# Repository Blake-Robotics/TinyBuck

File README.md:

# TinyBuck
A three channel Buck based high power led driver, with included AtTiny for programming

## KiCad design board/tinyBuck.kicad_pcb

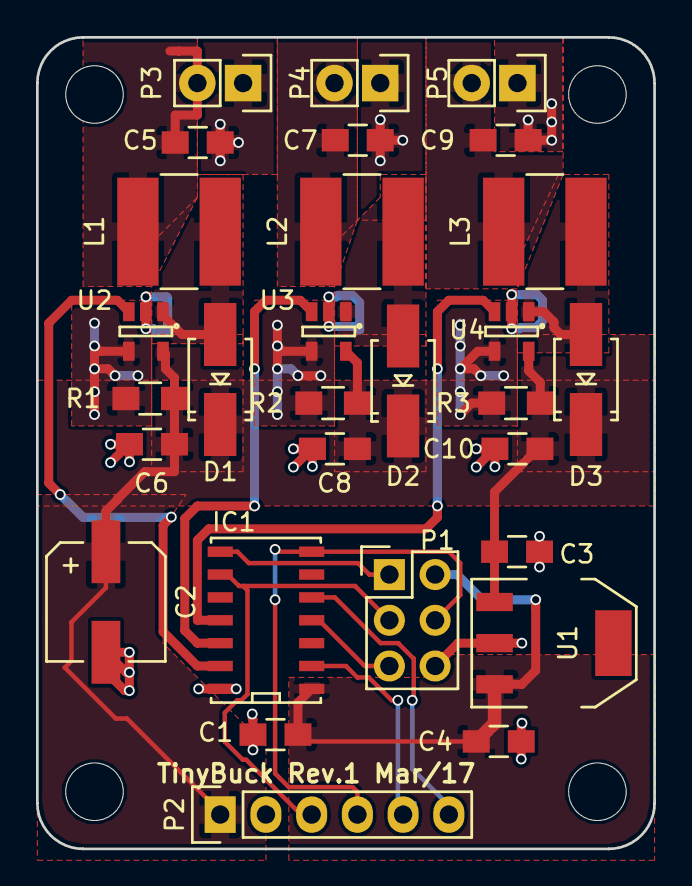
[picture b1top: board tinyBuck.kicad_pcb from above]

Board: 2 copper layers, 34.3 x 45.1 mm, 29 parts (0 on the bottom side), 21 nets.

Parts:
C1: C; C_0805_HandSoldering
C2: 22u; WURTH_ELECTRO
C3: 100n; C_0805_HandSoldering
C4, C6, C8, C10: 2u2; C_0805_HandSoldering
C5, C7, C9: 1u; C_0805_HandSoldering
D1, D2, D3: D_Schottky; SMA_Handsoldering
IC1: ATTINY24-SS; SOIC-14
L1, L2, L3: 33u; SRN6045
P1: CONN_02X03; Pin_Header_Straight_2x03
P2: CONN_01X06; Pin_Header_Straight_1x06
P3, P4, P5: CONN_01X02; Pin_Header_Straight_1x02
R1, R2, R3: 0R15; R_0805_HandSoldering
U1: LM7805CT; SOT-223
U2, U3, U4: AL8805; SOT-23-5

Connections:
+5V: C1.1, C4.2, IC1.1, P1.2, U1.3
/LED0+: C5.2, P3.1, R1.2, U2.4
/LED0-: C5.1, L1.1, P3.2
/LED1+: C7.2, P4.1, R2.2, U3.4
/LED1-: C7.1, L2.1, P4.2
/LED2+: C9.2, P5.1, R3.2, U4.4
/LED2-: C9.1, L3.1, P5.2
/PWM0: IC1.13, U2.3
/PWM1: IC1.12, U3.3
/PWM2: IC1.11, U4.3
/SCL: IC1.9, P1.3, P2.3
/SDA: IC1.7, P1.4, P2.4
/USR1: IC1.2, P2.5
/USR2: IC1.5, P2.6
/VIN: C2.1, C3.2, C6.1, C8.1, C10.1, D1.1, D2.1, D3.1, P2.1, R1.1, R2.1, R3.1, U1.1, U2.5, U3.5, U4.5
GND: C1.2, C2.2, C3.1, C4.1, C6.2, C8.2, C10.2, IC1.14, P1.6, P2.2, U1.2, U2.2, U3.2, U4.2
unnamed: D1.2, L1.2, U2.1
unnamed: D2.2, L2.2, U3.1
unnamed: D3.2, L3.2, U4.1
unnamed: IC1.4, P1.5
unnamed: IC1.8, P1.1

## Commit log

2017-04-14 Initial commit of firmware for project
2017-04-14 First commit of electronics parts, including V1 of Gebers
2017-04-21 Main header cleanup
